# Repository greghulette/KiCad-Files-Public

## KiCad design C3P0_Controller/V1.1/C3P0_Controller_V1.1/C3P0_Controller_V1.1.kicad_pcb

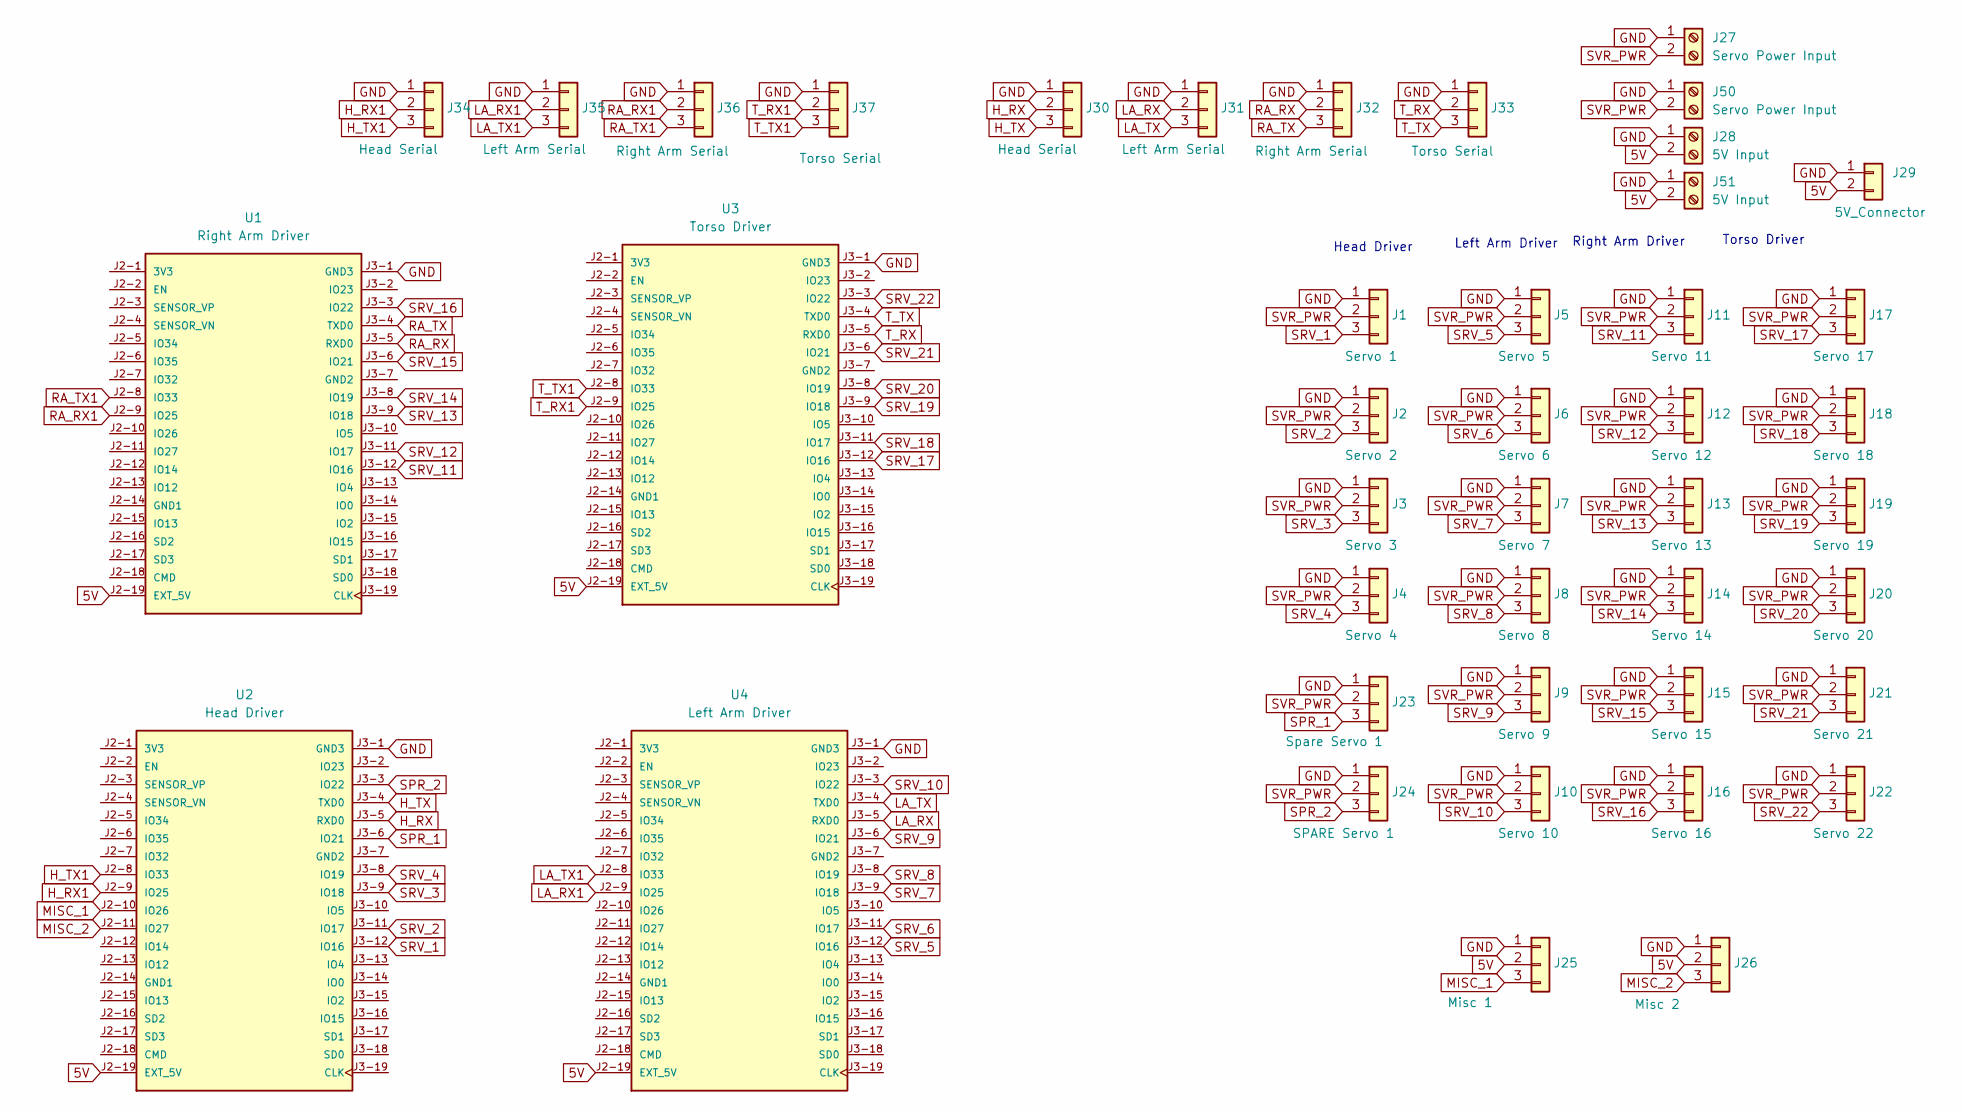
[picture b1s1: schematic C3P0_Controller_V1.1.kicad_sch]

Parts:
J1: Servo 1; PinHeader_1x03_P2.54mm_Vertical
J2: Servo 2; PinHeader_1x03_P2.54mm_Vertical
J3: Servo 3; PinHeader_1x03_P2.54mm_Vertical
J4: Servo 4; PinHeader_1x03_P2.54mm_Vertical
J5: Servo 5; PinHeader_1x03_P2.54mm_Vertical
J6: Servo 6; PinHeader_1x03_P2.54mm_Vertical
J7: Servo 7; PinHeader_1x03_P2.54mm_Vertical
J8: Servo 8; PinHeader_1x03_P2.54mm_Vertical
J9: Servo 9; PinHeader_1x03_P2.54mm_Vertical
J10: Servo 10; PinHeader_1x03_P2.54mm_Vertical
J11: Servo 11; PinHeader_1x03_P2.54mm_Vertical
J12: Servo 12; PinHeader_1x03_P2.54mm_Vertical
J13: Servo 13; PinHeader_1x03_P2.54mm_Vertical
J14: Servo 14; PinHeader_1x03_P2.54mm_Vertical
J15: Servo 15; PinHeader_1x03_P2.54mm_Vertical
J16: Servo 16; PinHeader_1x03_P2.54mm_Vertical
J17: Servo 17; PinHeader_1x03_P2.54mm_Vertical
J18: Servo 18; PinHeader_1x03_P2.54mm_Vertical
J19: Servo 19; PinHeader_1x03_P2.54mm_Vertical
J20: Servo 20; PinHeader_1x03_P2.54mm_Vertical
J21: Servo 21; PinHeader_1x03_P2.54mm_Vertical
J22: Servo 22; PinHeader_1x03_P2.54mm_Vertical
J23: Spare Servo 1; PinHeader_1x03_P2.54mm_Vertical
J24: SPARE Servo 1; PinHeader_1x03_P2.54mm_Vertical
J25: Misc 1; PinHeader_1x03_P2.54mm_Vertical
J26: Misc 2; PinHeader_1x03_P2.54mm_Vertical
J27, J50: Servo Power Input; TerminalBlock_Phoenix_MKDS-1,5-2-5.08_1x02_P5.08mm_Horizont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
J28, J51: 5V Input; TerminalBlock_Phoenix_MKDS-1,5-2-5.08_1x02_P5.08mm_Horizont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
J29: 5V_Connector; PinHeader_1x02_P2.54mm_Vertical
J30, J34: Head Serial; PinHeader_1x03_P2.54mm_Vertical
J31, J35: Left Arm Serial; PinHeader_1x03_P2.54mm_Vertical
J32, J36: Right Arm Serial; PinHeader_1x03_P2.54mm_Vertical
J33, J37: Torso Serial; PinHeader_1x03_P2.54mm_Vertical
U1: Right Arm Driver; MODULE_ESP32-DEVKITC-32D; PARTREV V4
U2: Head Driver; MODULE_ESP32-DEVKITC-32D; PARTREV V4
U3: Torso Driver; MODULE_ESP32-DEVKITC-32D; PARTREV V4
U4: Left Arm Driver; MODULE_ESP32-DEVKITC-32D; PARTREV V4

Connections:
5V: J25.2, J26.2, J28.2, J29.2, J51.2, U1.J2-19 (EXT_5V), U2.J2-19 (EXT_5V), U3.J2-19 (EXT_5V), U4.J2-19 (EXT_5V)
GND: J1.1, J2.1, J3.1, J4.1, J5.1, J6.1, J7.1, J8.1, J9.1, J10.1, J11.1, J12.1, J13.1, J14.1, J15.1, J16.1, J17.1, J18.1, J19.1, J20.1, J21.1, J22.1, J23.1, J24.1, J25.1, J26.1, J27.1, J28.1, J29.1, J30.1, J31.1, J32.1, J33.1, J34.1, J35.1, J36.1, J37.1, J50.1, J51.1, U1.J3-1 (GND3), U2.J3-1 (GND3), U3.J3-1 (GND3), U4.J3-1 (GND3)
H_RX: J30.2, U2.J3-5 (RXD0)
H_RX1: J34.2, U2.J2-9 (IO25)
H_TX: J30.3, U2.J3-4 (TXD0)
H_TX1: J34.3, U2.J2-8 (IO33)
LA_RX: J31.2, U4.J3-5 (RXD0)
LA_RX1: J35.2, U4.J2-9 (IO25)
LA_TX: J31.3, U4.J3-4 (TXD0)
LA_TX1: J35.3, U4.J2-8 (IO33)
MISC_1: J25.3, U2.J2-10 (IO26)
MISC_2: J26.3, U2.J2-11 (IO27)
RA_RX: J32.2, U1.J3-5 (RXD0)
RA_RX1: J36.2, U1.J2-9 (IO25)
RA_TX: J32.3, U1.J3-4 (TXD0)
RA_TX1: J36.3, U1.J2-8 (IO33)
SPR_1: J23.3, U2.J3-6 (IO21)
SPR_2: J24.3, U2.J3-3 (IO22)
SRV_1: J1.3, U2.J3-12 (IO16)
SRV_2: J2.3, U2.J3-11 (IO17)
SRV_3: J3.3, U2.J3-9 (IO18)
SRV_4: J4.3, U2.J3-8 (IO19)
SRV_5: J5.3, U4.J3-12 (IO16)
SRV_6: J6.3, U4.J3-11 (IO17)
SRV_7: J7.3, U4.J3-9 (IO18)
SRV_8: J8.3, U4.J3-8 (IO19)
SRV_9: J9.3, U4.J3-6 (IO21)
SRV_10: J10.3, U4.J3-3 (IO22)
SRV_11: J11.3, U1.J3-12 (IO16)
SRV_12: J12.3, U1.J3-11 (IO17)
SRV_13: J13.3, U1.J3-9 (IO18)
SRV_14: J14.3, U1.J3-8 (IO19)
SRV_15: J15.3, U1.J3-6 (IO21)
SRV_16: J16.3, U1.J3-3 (IO22)
SRV_17: J17.3, U3.J3-12 (IO16)
SRV_18: J18.3, U3.J3-11 (IO17)
SRV_19: J19.3, U3.J3-9 (IO18)
SRV_20: J20.3, U3.J3-8 (IO19)
SRV_21: J21.3, U3.J3-6 (IO21)
SRV_22: J22.3, U3.J3-3 (IO22)
SVR_PWR: J1.2, J2.2, J3.2, J4.2, J5.2, J6.2, J7.2, J8.2, J9.2, J10.2, J11.2, J12.2, J13.2, J14.2, J15.2, J16.2, J17.2, J18.2, J19.2, J20.2, J21.2, J22.2, J23.2, J24.2, J27.2, J50.2
T_RX: J33.2, U3.J3-5 (RXD0)
T_RX1: J37.2, U3.J2-9 (IO25)
T_TX: J33.3, U3.J3-4 (TXD0)
T_TX1: J37.3, U3.J2-8 (IO33)

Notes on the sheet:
Torso Driver
Head Driver
Left Arm Driver
Right Arm Driver

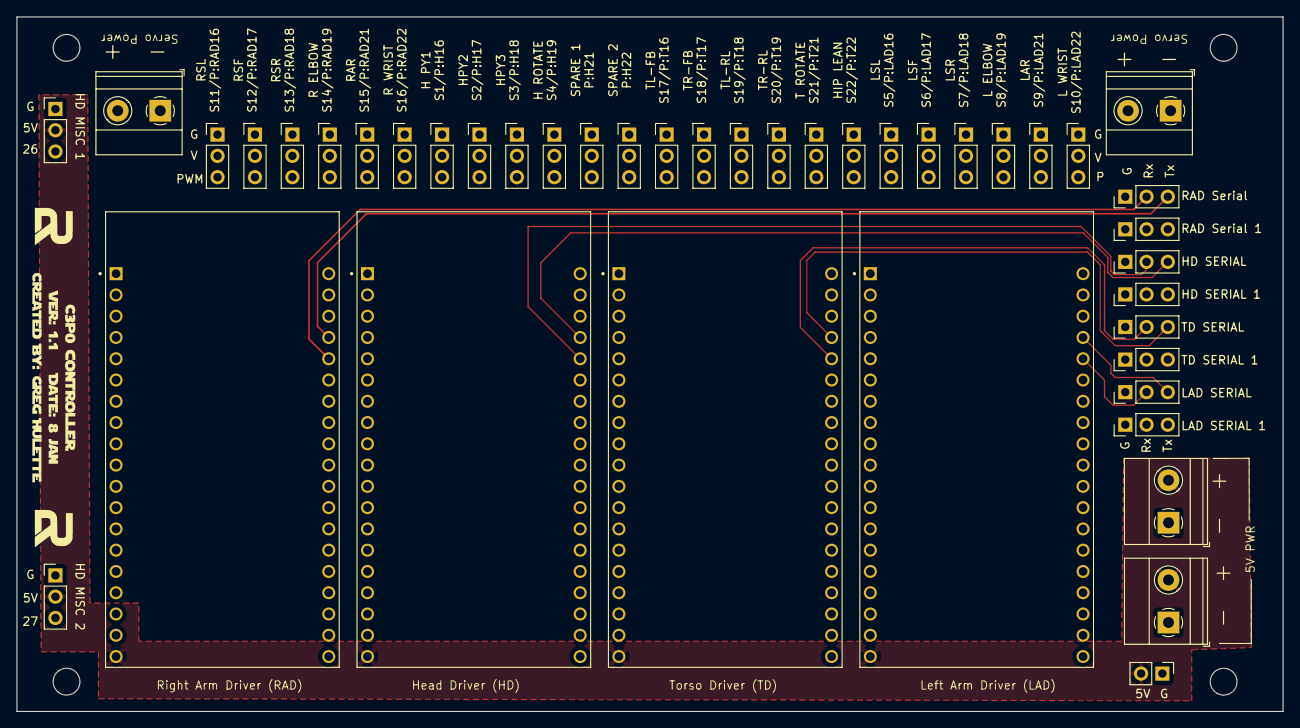
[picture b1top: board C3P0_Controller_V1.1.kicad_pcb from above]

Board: 4 copper layers, 151.2 x 82.9 mm, 43 parts (0 on the bottom side), 45 nets.

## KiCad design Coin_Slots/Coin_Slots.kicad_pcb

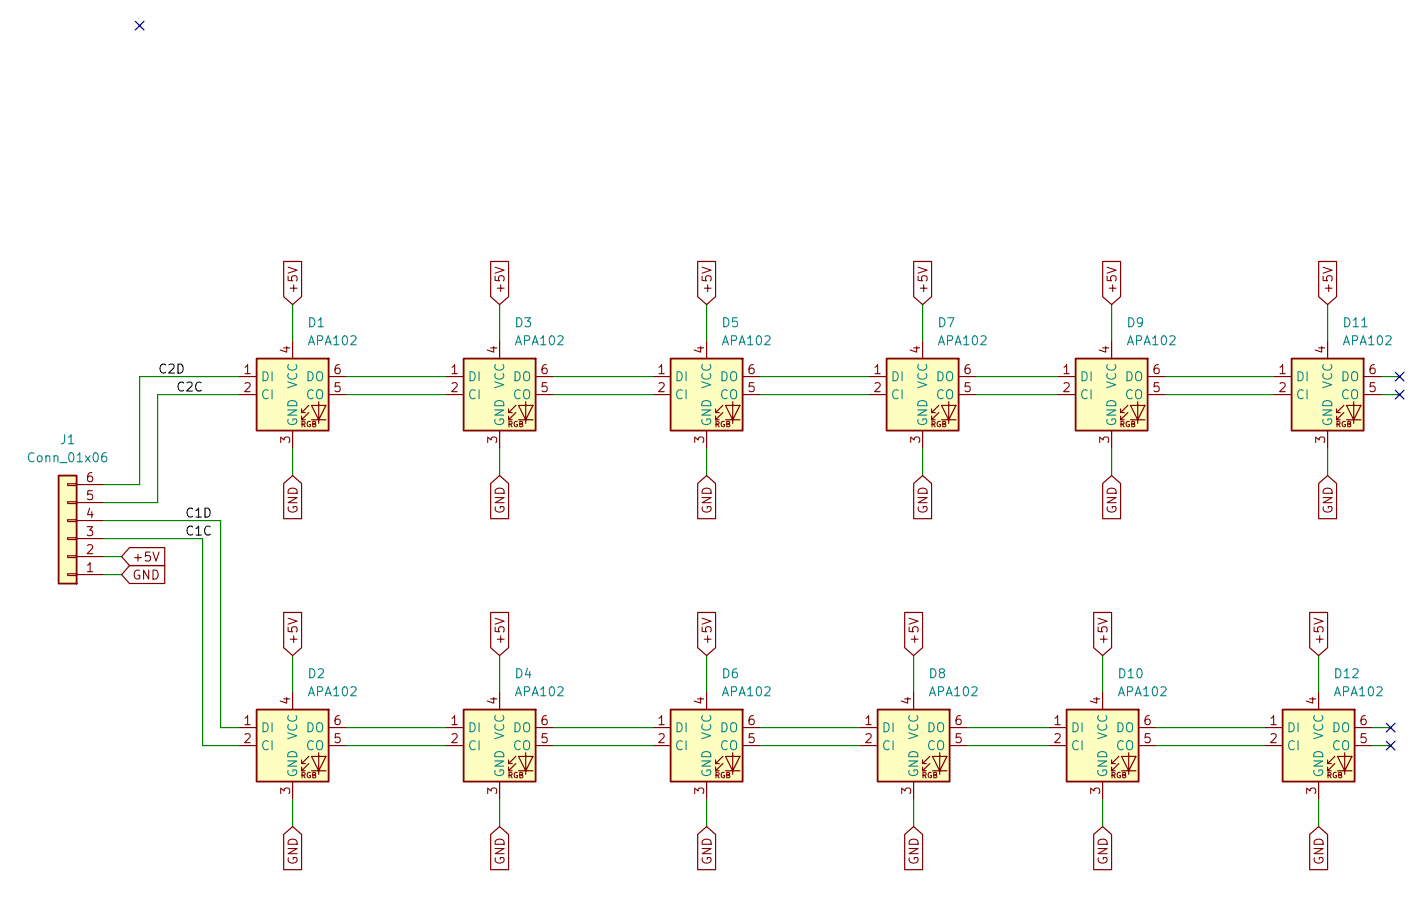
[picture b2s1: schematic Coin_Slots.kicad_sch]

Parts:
D1, D2, D3, D4, D5, D6, D7, D8, D9, D10, D11, D12: APA102; LED_RGB_5050-6
J1: Conn_01x06; PinHeader_1x06_P2.54mm_Vertical

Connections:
+5V: D1.4 (VCC), D2.4 (VCC), D3.4 (VCC), D4.4 (VCC), D5.4 (VCC), D6.4 (VCC), D7.4 (VCC), D8.4 (VCC), D9.4 (VCC), D10.4 (VCC), D11.4 (VCC), D12.4 (VCC), J1.2
/C1C: D2.2 (CI), J1.3
/C1D: D2.1 (DI), J1.4
/C2C: D1.2 (CI), J1.5
/C2D: D1.1 (DI), J1.6
GND: D1.3 (GND), D2.3 (GND), D3.3 (GND), D4.3 (GND), D5.3 (GND), D6.3 (GND), D7.3 (GND), D8.3 (GND), D9.3 (GND), D10.3 (GND), D11.3 (GND), D12.3 (GND), J1.1
unnamed: D1.5 (CO), D3.2 (CI)
unnamed: D1.6 (DO), D3.1 (DI)
unnamed: D2.5 (CO), D4.2 (CI)
unnamed: D2.6 (DO), D4.1 (DI)
unnamed: D3.5 (CO), D5.2 (CI)
unnamed: D3.6 (DO), D5.1 (DI)
unnamed: D4.6 (DO), D6.1 (DI)
unnamed: D4.5 (CO), D6.2 (CI)
unnamed: D5.6 (DO), D7.1 (DI)
unnamed: D5.5 (CO), D7.2 (CI)
unnamed: D6.6 (DO), D8.1 (DI)
unnamed: D6.5 (CO), D8.2 (CI)
unnamed: D7.6 (DO), D9.1 (DI)
unnamed: D7.5 (CO), D9.2 (CI)
unnamed: D9.5 (CO), D11.2 (CI)
unnamed: D9.6 (DO), D11.1 (DI)
unnamed: D8.6 (DO), D10.1 (DI)
unnamed: D8.5 (CO), D10.2 (CI)
unnamed: D10.6 (DO), D12.1 (DI)
unnamed: D10.5 (CO), D12.2 (CI)

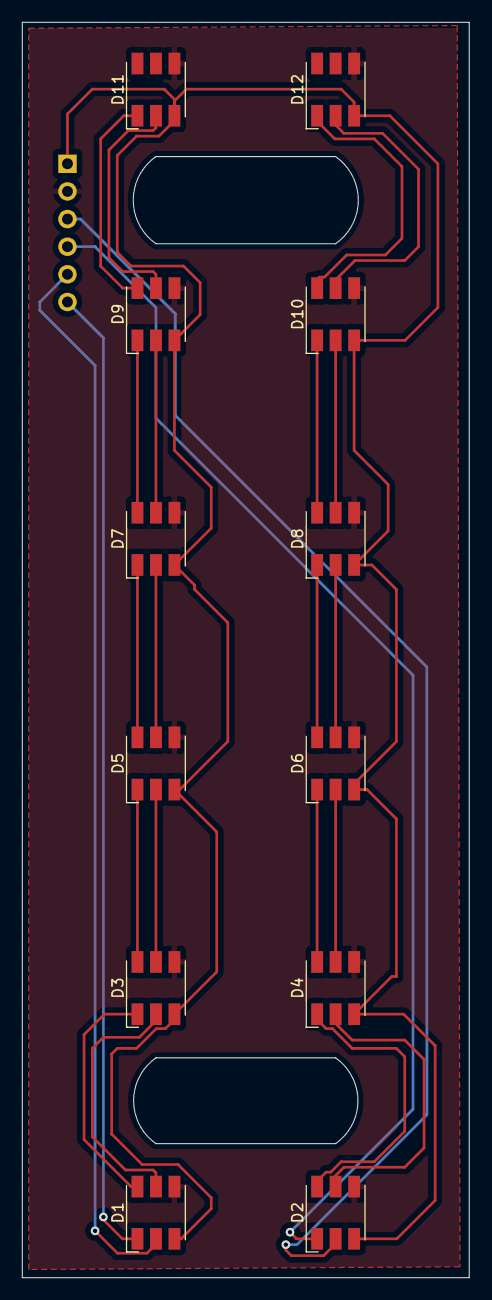
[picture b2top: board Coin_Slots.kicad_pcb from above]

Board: 2 copper layers, 41.1 x 115.3 mm, 13 parts (1 on the bottom side), 26 nets.

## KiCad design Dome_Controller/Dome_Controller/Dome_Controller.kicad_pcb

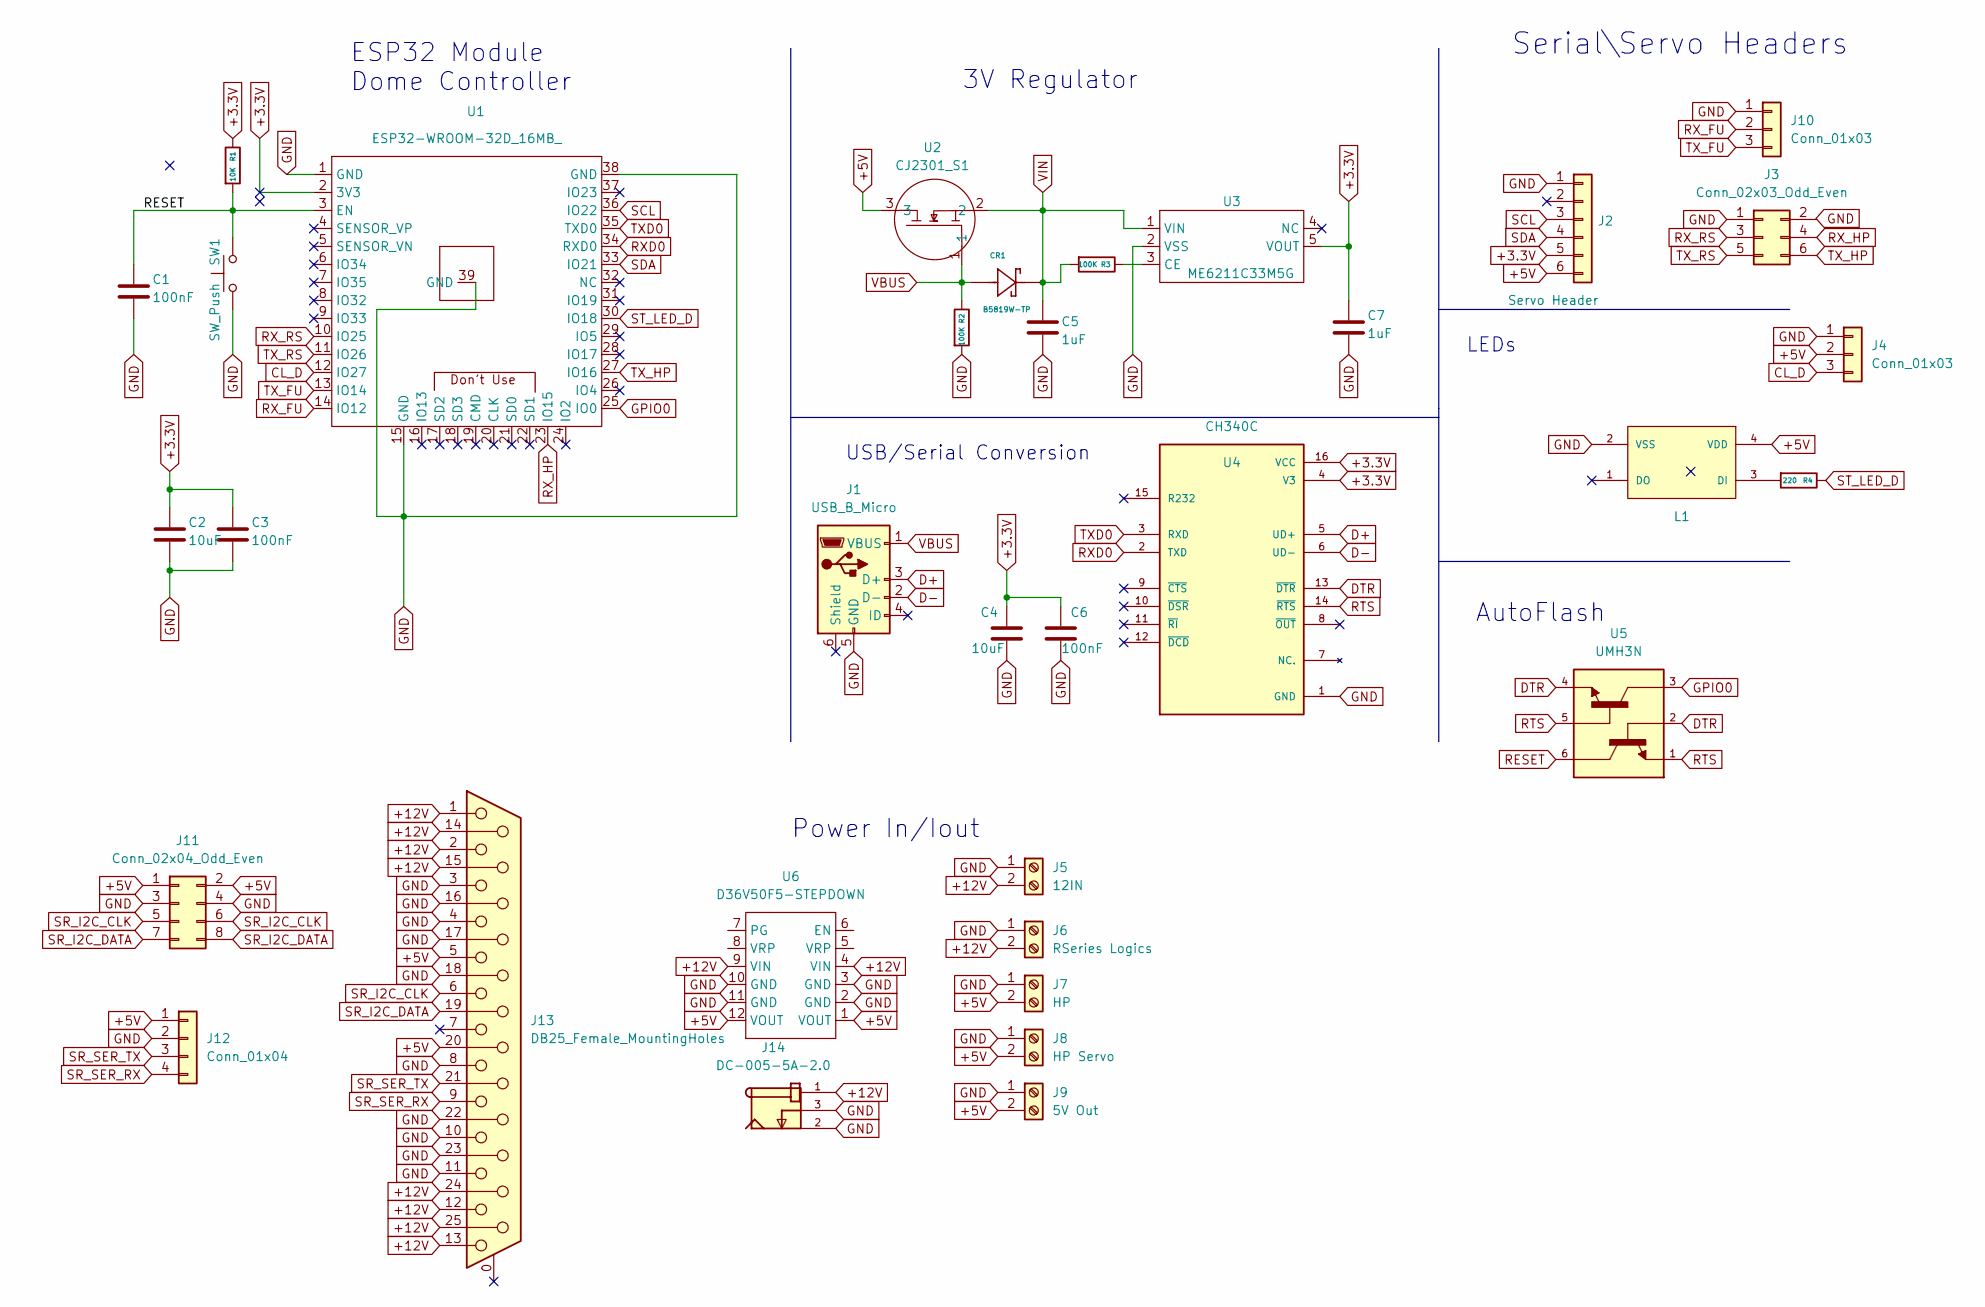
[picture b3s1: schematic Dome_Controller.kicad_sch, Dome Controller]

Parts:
C1, C3, C6: 100nF; C_0402_1005Metric; LCSC C307331
C2, C4: 10uF; C_0402_1005Metric; LCSC C315248
C5, C7: 1uF; C_0402_1005Metric; LCSC C77009
CR1: B5819W-TP; SOD3716X135N; LCSC C84354
J1: USB_B_Micro; USB_Micro-B_Amphenol_10118194_Horizontal; LCSC C132563
J2: Servo Header; PinHeader_1x06_P2.54mm_Vertical; LCSC C37208
J3: Conn_02x03_Odd_Even; PinHeader_2x03_P2.54mm_Vertical; LCSC C492420
J4, J10: Conn_01x03; PinHeader_1x03_P2.54mm_Vertical; LCSC C49257
J5: 12IN; TerminalBlock_4Ucon_1x02_P3.50mm_Horizontal; LCSC C474892
J6: RSeries Logics; TerminalBlock_4Ucon_1x02_P3.50mm_Horizontal; LCSC C474892
J7: HP; TerminalBlock_4Ucon_1x02_P3.50mm_Horizontal; LCSC C474892
J8: HP Servo; TerminalBlock_4Ucon_1x02_P3.50mm_Horizontal; LCSC C474892
J9: 5V Out; TerminalBlock_4Ucon_1x02_P3.50mm_Horizontal; LCSC C474892
J11: Conn_02x04_Odd_Even; PinHeader_2x04_P2.54mm_Vertical; LCSC C706894
J12: Conn_01x04; PinHeader_1x04_P2.54mm_Vertical; LCSC C358686
J13: DB25_Female_MountingHoles; DSUB-25_Female_Vertical_P2.77x2.84mm_MountingHoles; LCSC C77833
J14: DC-005-5A-2.0; XKB_DC-005-5A-2.0; PARTREV A0; LCSC C381116
L1: WS2812B-2020; LCSC C965555
R1: 10K; R_0603_1608Metric; LCSC C269701
R2, R3: 100K; R_0603_1608Metric; LCSC C25803
R4: 220; R_0402_1005Metric; LCSC C25091
SW1: SW_Push; TS-1101S-B-B-B-W-A; LCSC C692465
U1: ESP32-WROOM-32D_16MB_; ESP32-WROOM-32; LCSC C529578
U2: CJ2301_S1; SOT-23; LCSC C8547
U3: ME6211C33M5G; SOT-23-5; LCSC C82942
U4: CH340C; SOIC127P600X180-16N; PARTREV 2G; LCSC C84681
U5: UMH3N; UMT6; LCSC C62892
U6: D36V50F5-STEPDOWN

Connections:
+3.3V: C2.1, C3.1, C4.1, C6.1, C7.1, J2.5, R1.1, U1.2 (3V3), U3.5 (VOUT), U4.4 (V3), U4.16 (VCC)
+5V: J2.6, J4.2, J7.2, J8.2, J9.2, J11.1, J11.2, J12.1, J13.5, J13.20, L1.4 (VDD), U2.3, U6.1 (VOUT), U6.12 (VOUT)
+12V: J5.2, J6.2, J13.1, J13.2, J13.12, J13.13, J13.14, J13.15, J13.24, J13.25, J14.1, U6.4 (VIN), U6.9 (VIN)
CL_D: J4.3, U1.12 (IO27)
D+: J1.3 (D+), U4.5 (UD+)
D-: J1.2 (D-), U4.6 (UD-)
DTR: U4.13 (~DTR), U5.2, U5.4
GND: C1.2, C2.2, C3.2, C4.2, C5.1, C6.2, C7.2, J1.5 (GND), J2.1, J3.1, J3.2, J4.1, J5.1, J6.1, J7.1, J8.1, J9.1, J10.1, J11.3, J11.4, J12.2, J13.3, J13.4, J13.8, J13.10, J13.11, J13.16, J13.17, J13.18, J13.22, J13.23, J14.2, J14.3, L1.2 (VSS), R2.2, SW1.1, U1.1 (GND), U1.15 (GND), U1.38 (GND), U1.39 (GND), U3.2 (VSS), U4.1 (GND), U6.2 (GND), U6.3 (GND), U6.10 (GND), U6.11 (GND)
GPIO0: U1.25 (IO0), U5.3
unnamed: L1.3 (DI), R4.2
unnamed: R3.1, U3.3 (CE)
RESET: C1.1, R1.2, SW1.2, U1.3 (EN), U5.6
RTS: U4.14 (~RTS), U5.1, U5.5
RXD0: U1.34 (RXD0), U4.2 (TXD)
RX_FU: J10.2, U1.14 (IO12)
RX_HP: J3.4, U1.23 (IO15)
RX_RS: J3.3, U1.10 (IO25)
SCL: J2.3, U1.36 (IO22)
SDA: J2.4, U1.33 (IO21)
SR_I2C_CLK: J11.5, J11.6, J13.6
SR_I2C_DATA: J11.7, J11.8, J13.19
SR_SER_RX: J12.4, J13.9
SR_SER_TX: J12.3, J13.21
ST_LED_D: R4.1, U1.30 (IO18)
TXD0: U1.35 (TXD0), U4.3 (RXD)
TX_FU: J10.3, U1.13 (IO14)
TX_HP: J3.6, U1.27 (IO16)
TX_RS: J3.5, U1.11 (IO26)
VBUS: CR1.A, J1.1 (VBUS), R2.1, U2.1
VIN: C5.2, CR1.C, R3.2, U2.2, U3.1 (VIN)

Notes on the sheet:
ESP32 Module Dome Controller
3V Regulator
LEDs
Power In/Iout
USB/Serial Conversion
AutoFlash
Serial\Servo Headers

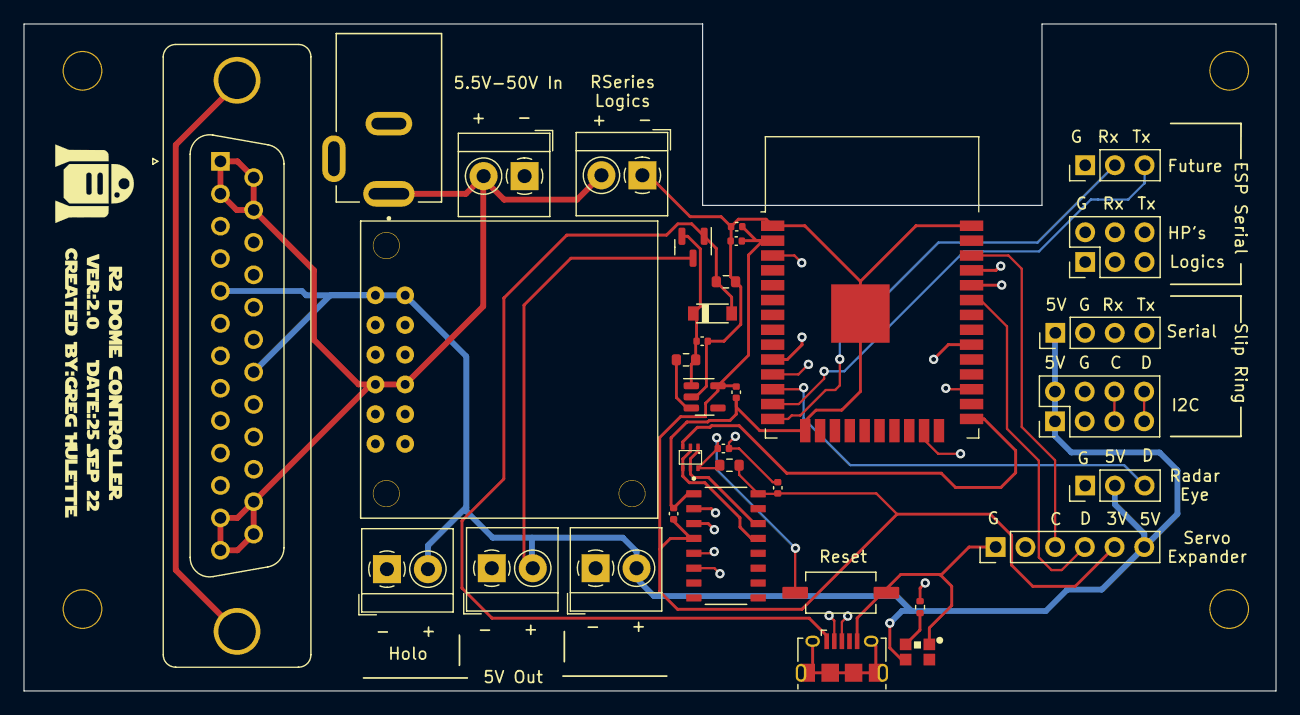
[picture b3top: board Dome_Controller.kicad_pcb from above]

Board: 4 copper layers, 107.0 x 57.0 mm, 34 parts (0 on the bottom side), 30 nets.

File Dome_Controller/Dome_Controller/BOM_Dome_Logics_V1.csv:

Comment,Designator,Footprint,LCSC
100nF,"C1,C3,C6",Capacitor_SMD:C_0402_1005Metric,C307331
10uF,"C2,C4",Capacitor_SMD:C_0402_1005Metric,C315248
1uF,"C5,C7",Capacitor_SMD:C_0402_1005Metric,C77009
B5819W-TP,CR1,Custom:SOD3716X135N,C84354
USB_B_Micro,J1,Connector_USB:USB_Micro-B_Amphenol_10118194_Horizontal,C132563
SERIAL_FU,J12,Connector_Molex:Molex_KK-254_AE-6410-03A_1x03_P2.54mm_Vertical,C471416
Conn_01x04,J2,Connector_Molex:Molex_KK-254_AE-6410-04A_1x04_P2.54mm_Vertical,C240840
Front Logics,J3,Connector_Molex:Molex_KK-254_AE-6410-03A_1x03_P2.54mm_Vertical,C471416
12OUT,J5,TerminalBlock_4Ucon:TerminalBlock_4Ucon_1x02_P3.50mm_Horizontal,C474892
5V OUT,J7,TerminalBlock_4Ucon:TerminalBlock_4Ucon_1x02_P3.50mm_Horizontal,C474892
WS2812B-2020,L1,WS2812B-2020,C965555
10K,R1,Resistor_SMD:R_0603_1608Metric,C269701
100K,"R2,R3",Resistor_SMD:R_0603_1608Metric,C25803
220,R4,Resistor_SMD:R_0402_1005Metric,C25091
SW_Push,SW1,Custom:TS-1101S-B-B-B-W-A,C692465
ESP32-WROOM-32D_16MB_,U1,RF_Module:ESP32-WROOM-32,C529578
CJ2301_S1,U2,Package_TO_SOT_SMD:SOT-23,C8547
ME6211C33M5G,U3,Package_TO_SOT_SMD:SOT-23-5,C82942
CH340C,U4,Custom:SOIC127P600X180-16N,C84681
UMH3N,U5,Custom:UMT6,C62892

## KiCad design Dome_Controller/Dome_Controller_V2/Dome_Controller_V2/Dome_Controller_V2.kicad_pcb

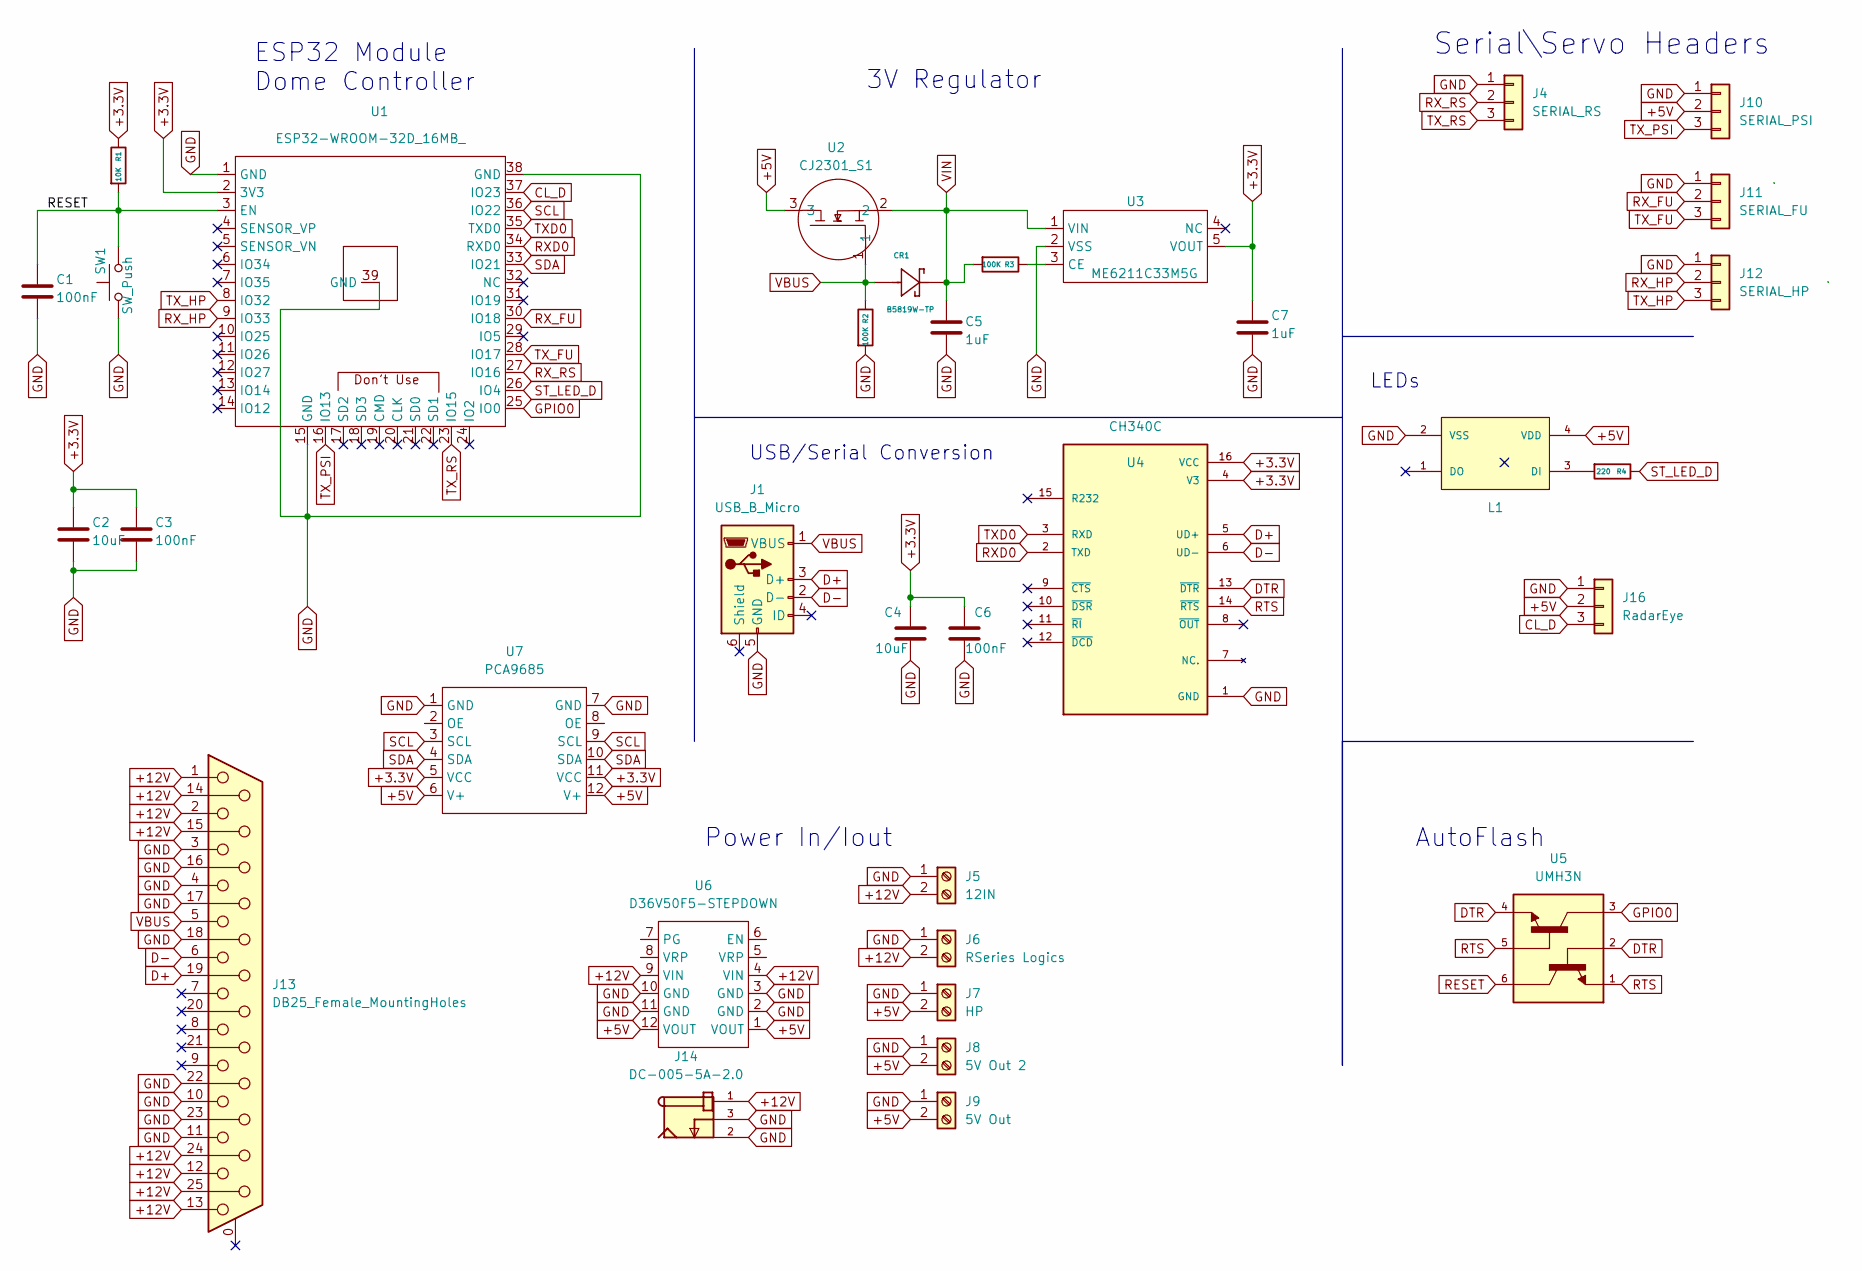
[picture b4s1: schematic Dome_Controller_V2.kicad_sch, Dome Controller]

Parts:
C1, C3, C6: 100nF; C_0402_1005Metric; LCSC C307331
C2, C4: 10uF; C_0402_1005Metric; LCSC C315248
C5, C7: 1uF; C_0402_1005Metric; LCSC C77009
CR1: B5819W-TP; SOD3716X135N; LCSC C84354
J1: USB_B_Micro; USB_Micro-B_Amphenol_10118194_Horizontal; LCSC C132563
J4: SERIAL_RS; Molex_KK-254_AE-6410-03A_1x03_P2.54mm_Vertical; LCSC C471416
J5: 12IN; TerminalBlock_4Ucon_1x02_P3.50mm_Horizontal; LCSC C474892
J6: RSeries Logics; TerminalBlock_4Ucon_1x02_P3.50mm_Horizontal; LCSC C474892
J7: HP; TerminalBlock_4Ucon_1x02_P3.50mm_Horizontal; LCSC C474892
J8: 5V Out 2; TerminalBlock_4Ucon_1x02_P3.50mm_Horizontal; LCSC C474892
J9: 5V Out; TerminalBlock_4Ucon_1x02_P3.50mm_Horizontal; LCSC C474892
J10: SERIAL_PSI; Molex_KK-254_AE-6410-03A_1x03_P2.54mm_Vertical; LCSC C471416
J11: SERIAL_FU; Molex_KK-254_AE-6410-03A_1x03_P2.54mm_Vertical; LCSC C471416
J12: SERIAL_HP; Molex_KK-254_AE-6410-03A_1x03_P2.54mm_Vertical; LCSC C471416
J13: DB25_Female_MountingHoles; DSUB-25_Female_Vertical_P2.77x2.84mm_MountingHoles; LCSC C77833
J14: DC-005-5A-2.0; XKB_DC-005-5A-2.0; PARTREV A0; LCSC C381116
J16: RadarEye; Molex_KK-254_AE-6410-03A_1x03_P2.54mm_Vertical; LCSC C471416
L1: WS2812B-2020; LCSC C965555
R1: 10K; R_0603_1608Metric; LCSC C269701
R2, R3: 100K; R_0603_1608Metric; LCSC C25803
R4: 220; R_0402_1005Metric; LCSC C25091
SW1: SW_Push; TS-1101S-B-B-B-W-A; LCSC C692465
U1: ESP32-WROOM-32D_16MB_; ESP32-WROOM-32; LCSC C529578
U2: CJ2301_S1; SOT-23; LCSC C8547
U3: ME6211C33M5G; SOT-23-5; LCSC C82942
U4: CH340C; SOIC127P600X180-16N; PARTREV 2G; LCSC C84681
U5: UMH3N; UMT6; LCSC C62892
U6: D36V50F5-STEPDOWN
U7: PCA9685

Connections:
+3.3V: C2.1, C3.1, C4.1, C6.1, C7.1, R1.1, U1.2 (3V3), U3.5 (VOUT), U4.4 (V3), U4.16 (VCC), U7.5 (VCC), U7.11 (VCC)
+5V: J7.2, J8.2, J9.2, J10.2, J16.2, L1.4 (VDD), U2.3, U6.1 (VOUT), U6.12 (VOUT), U7.6 (V+), U7.12 (V+)
+12V: J5.2, J6.2, J13.1, J13.2, J13.12, J13.13, J13.14, J13.15, J13.24, J13.25, J14.1, U6.4 (VIN), U6.9 (VIN)
CL_D: J16.3, U1.37 (IO23)
D+: J1.3 (D+), J13.19, U4.5 (UD+)
D-: J1.2 (D-), J13.6, U4.6 (UD-)
DTR: U4.13 (~DTR), U5.2, U5.4
GND: C1.2, C2.2, C3.2, C4.2, C5.1, C6.2, C7.2, J1.5 (GND), J4.1, J5.1, J6.1, J7.1, J8.1, J9.1, J10.1, J11.1, J12.1, J13.3, J13.4, J13.10, J13.11, J13.16, J13.17, J13.18, J13.22, J13.23, J14.2, J14.3, J16.1, L1.2 (VSS), R2.2, SW1.1, U1.1 (GND), U1.15 (GND), U1.38 (GND), U1.39 (GND), U3.2 (VSS), U4.1 (GND), U6.2 (GND), U6.3 (GND), U6.10 (GND), U6.11 (GND), U7.1 (GND), U7.7 (GND)
GPIO0: U1.25 (IO0), U5.3
unnamed: L1.3 (DI), R4.2
unnamed: R3.1, U3.3 (CE)
RESET: C1.1, R1.2, SW1.2, U1.3 (EN), U5.6
RTS: U4.14 (~RTS), U5.1, U5.5
RXD0: U1.34 (RXD0), U4.2 (TXD)
RX_FU: J11.2, U1.30 (IO18)
RX_HP: J12.2, U1.9 (IO33)
RX_RS: J4.2, U1.27 (IO16)
SCL: U1.36 (IO22), U7.3 (SCL), U7.9 (SCL)
SDA: U1.33 (IO21), U7.4 (SDA), U7.10 (SDA)
ST_LED_D: R4.1, U1.26 (IO4)
TXD0: U1.35 (TXD0), U4.3 (RXD)
TX_FU: J11.3, U1.28 (IO17)
TX_HP: J12.3, U1.8 (IO32)
TX_PSI: J10.3, U1.16 (IO13)
TX_RS: J4.3, U1.23 (IO15)
VBUS: CR1.A, J1.1 (VBUS), J13.5, R2.1, U2.1
VIN: C5.2, CR1.C, R3.2, U2.2, U3.1 (VIN)

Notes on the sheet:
ESP32 Module Dome Controller
3V Regulator
LEDs
Power In/Iout
USB/Serial Conversion
AutoFlash
Serial\Servo Headers

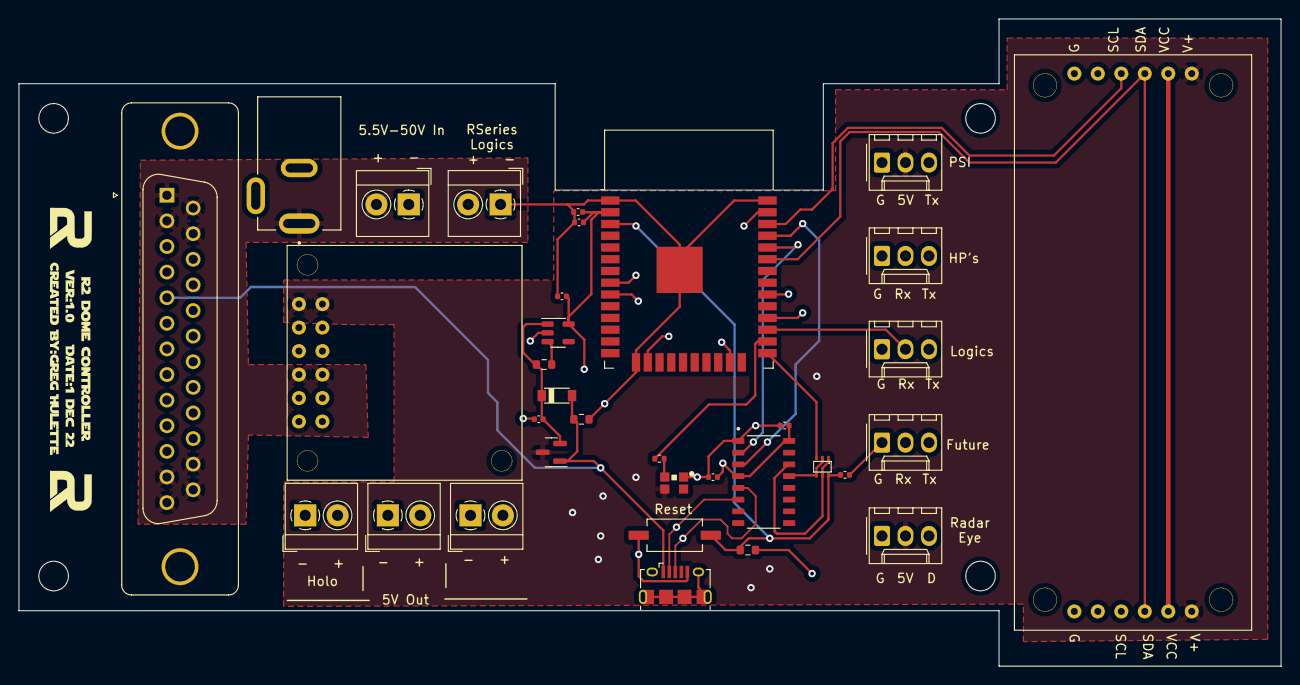
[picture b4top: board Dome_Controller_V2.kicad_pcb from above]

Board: 4 copper layers, 136.5 x 70.0 mm, 34 parts (0 on the bottom side), 27 nets.
